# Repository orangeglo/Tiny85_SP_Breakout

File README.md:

# Tiny85_SP_Breakout
Flex board breakout for the ATtiny85 SOIC package, designed for the Game Boy SP, but useful for anything!

## [Order on OSH Park](https://oshpark.com/shared_projects/h6Am5436)
I recommend ordering the flex board option!

## Parts
- ATtiny85 SOIC package
- 0603 0.1uF capacitor

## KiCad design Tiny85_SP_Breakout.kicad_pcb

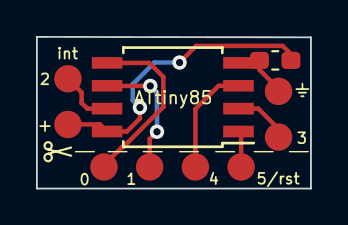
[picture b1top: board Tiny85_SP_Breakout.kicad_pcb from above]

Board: 2 copper layers, 15.2 x 8.4 mm, 5 parts (0 on the bottom side), 8 nets.

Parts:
C1: 0.1 uF; C_0603_1608Metric_Pad1.05x0.95mm_HandSolder
J1, J3: Conn_01x02_Female; 2_tiny_pads
J2: Conn_01x04_Female; 4_tiny_pads
U1: ATtiny85-20SU; SOIJ-8_5.3x5.3mm_P1.27mm

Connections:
GND: C1.2, J3.1, U1.4
unnamed: J1.2, U1.7
unnamed: J2.1, U1.5
unnamed: J2.2, U1.6
unnamed: J2.3, U1.3
unnamed: J2.4, U1.1
unnamed: J3.2, U1.2
VCC: C1.1, J1.1, U1.8

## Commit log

2020-03-14 Add kicad files
2020-03-14 Create LICENSE
2020-03-14 Add osh preview
2021-01-16 Update to v2
